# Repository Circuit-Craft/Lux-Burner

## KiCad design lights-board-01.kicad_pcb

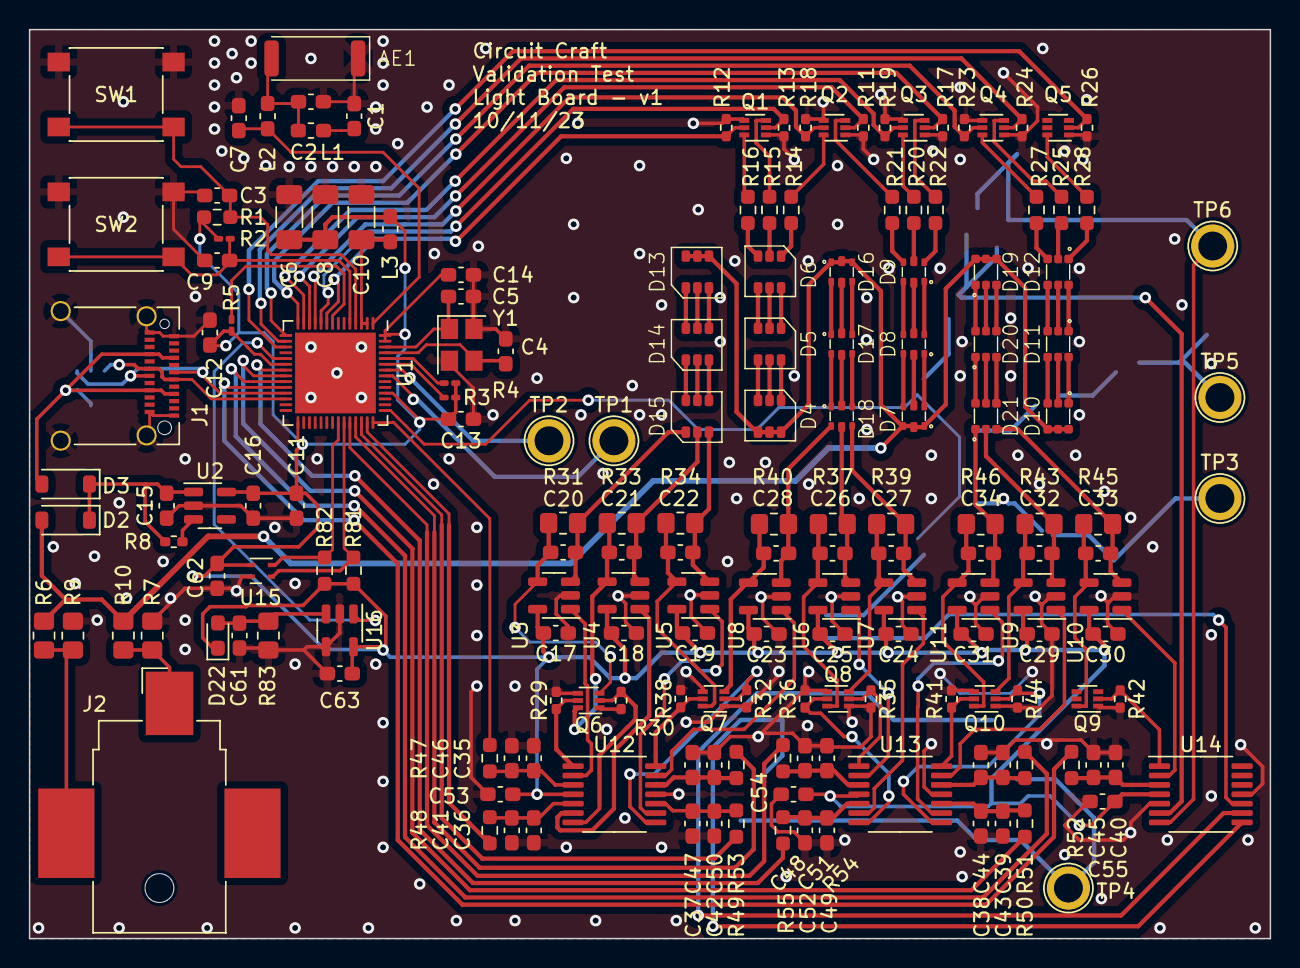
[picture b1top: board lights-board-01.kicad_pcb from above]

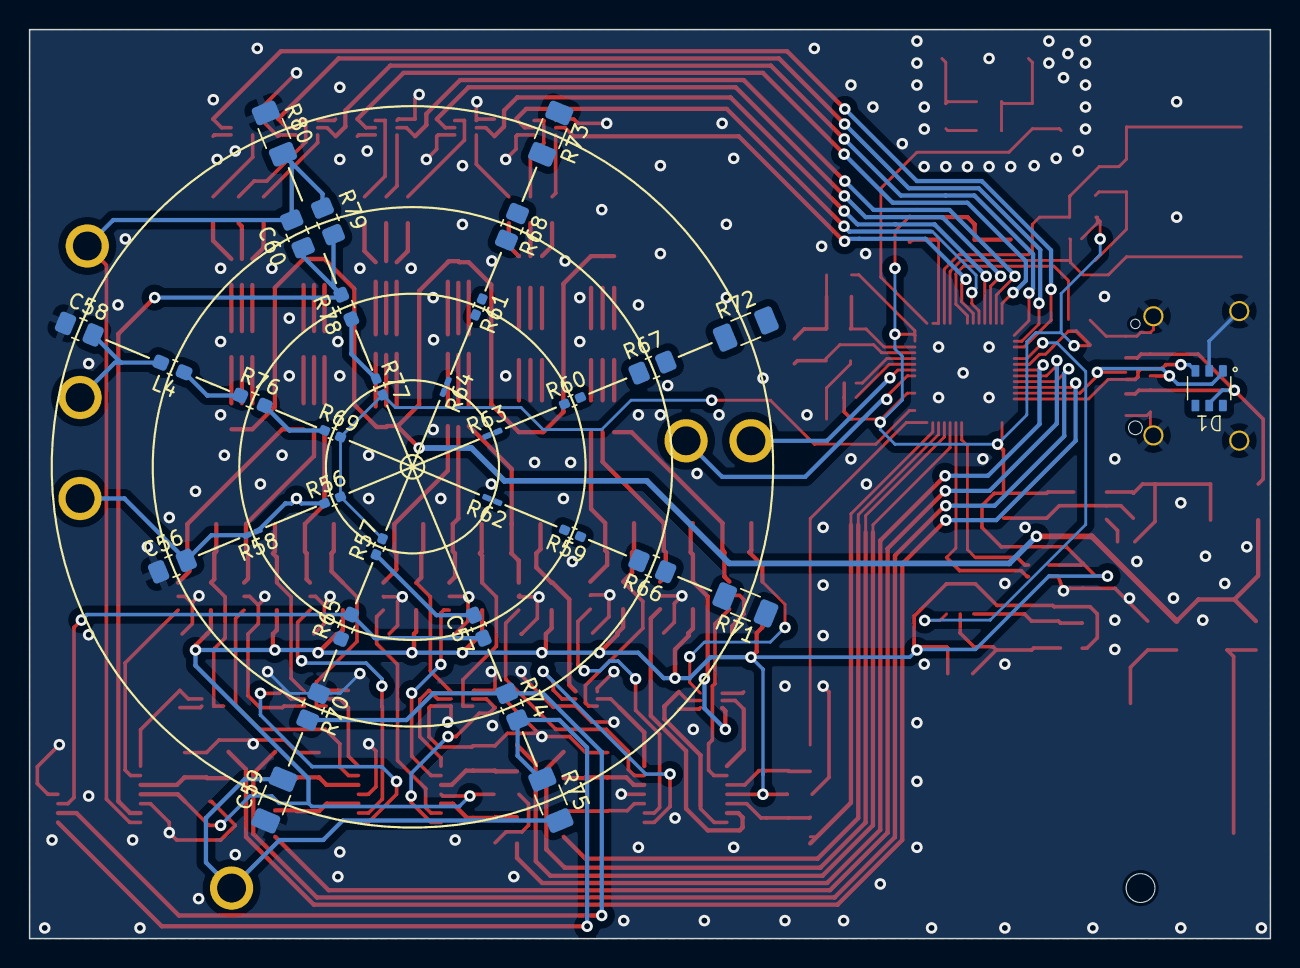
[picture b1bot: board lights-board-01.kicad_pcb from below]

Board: 2 copper layers, 86.0 x 63.0 mm, 210 parts (32 on the bottom side), 158 nets.

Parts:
AE1: Antenna_Chip; 2450AT43B
C1, C2, C3, C4, C5, C7: DNP; C_0603_1608Metric_Pad1.08x0.95mm_HandSolder
C6: 10uF; C_1206_3216Metric_Pad1.33x1.80mm_HandSolder
C8, C10, C59: 0.1uF; C_1206_3216Metric_Pad1.33x1.80mm_HandSolder
C9, C20, C21, C22, C26, C27, C28, C32, C33, C34, C35, C36, C37, C38, C39, C40, C41, C42, C43, C44, C45, C46, C47, C48, C49, C50, C51, C52, C57, C61: 0.1uF; C_0603_1608Metric_Pad1.08x0.95mm_HandSolder
C11, C12, C13, C14, C15, C16, C17, C18, C19, C23, C24, C25, C29, C30, C31, C53, C54, C55, C62, C63: 4.7uF; C_0603_1608Metric_Pad1.08x0.95mm_HandSolder
C56, C60: 0.1uF; C_0805_2012Metric_Pad1.18x1.45mm_HandSolder
C58: 10uF; C_0805_2012Metric_Pad1.18x1.45mm_HandSolder
D1: D5V0F4U6SO; SOT26
D2, D3: 1N4148; D_SOD-123
D4, D5, D6, D13, D14, D15: CLY6D
D7, D8, D9, D16, D17, D18: EAST1616; LED_RGB_EAST_PLCC-6
D10, D11, D12, D19, D20, D21: IN-S66TFT; LED_RGB_Inolux_PLCC-6
D22: IN-S63DTLS; D_0603_1608Metric_Pad1.05x0.95mm_HandSolder
J1: USB_C_Receptacle_USB2.0; USB_C_Receptacle_Amphenol_12401610E4-2A_CircularHoles
J2: Conn_01x02; BarrelJack_CUI_PJ-036AH-SMT_Horizontal
L1, L2: DNP; L_0603_1608Metric_Pad1.05x0.95mm_HandSolder
L3: 2nH; L_0603_1608Metric_Pad1.05x0.95mm_HandSolder
L4: 1uH; L_0603_1608Metric_Pad1.05x0.95mm_HandSolder
Q1, Q2, Q3, Q4, Q5, Q6, Q7, Q8, Q9, Q10: DMN2710UV; SOT-563
R1: DNP; R_0603_1608Metric_Pad0.98x0.95mm_HandSolder
R2, R3, R4, R5: 10k; R_0201_0603Metric_Pad0.64x0.40mm_HandSolder
R6, R7, R66, R67, R68: 0; R_0805_2012Metric_Pad1.20x1.40mm_HandSolder
R8, R11, R12, R13, R17, R18, R19, R23, R24, R26, R29, R30, R32, R35, R36, R38, R41, R42, R44: 100k; R_0402_1005Metric_Pad0.72x0.64mm_HandSolder
R9, R10: DNP; R_0805_2012Metric_Pad1.20x1.40mm_HandSolder
R14: 200; R_0603_1608Metric_Pad0.98x0.95mm_HandSolder
R15, R21, R22: 260; R_0603_1608Metric_Pad0.98x0.95mm_HandSolder
R16: 380; R_0603_1608Metric_Pad0.98x0.95mm_HandSolder
R20: 460; R_0603_1608Metric_Pad0.98x0.95mm_HandSolder
R25: 400; R_0603_1608Metric_Pad0.98x0.95mm_HandSolder
R27, R28: 240; R_0603_1608Metric_Pad0.98x0.95mm_HandSolder
R31, R33: 1.5; R_0805_2012Metric_Pad1.20x1.40mm_HandSolder
R34: 1; R_0805_2012Metric_Pad1.20x1.40mm_HandSolder
R37, R39, R40: 0.75; R_0805_2012Metric_Pad1.20x1.40mm_HandSolder
R43, R45, R46: 3; R_0805_2012Metric_Pad1.20x1.40mm_HandSolder
R47, R48, R49, R50, R51, R52, R53, R54, R55, R65, R76, R78: 1k; R_0603_1608Metric_Pad0.98x0.95mm_HandSolder
R56, R57, R59, R60, R61, R69, R77: 0; R_0402_1005Metric_Pad0.72x0.64mm_HandSolder
R58: 1k; R_0201_0603Metric_Pad0.64x0.40mm_HandSolder
R62, R63, R64: 0; R_0201_0603Metric_Pad0.64x0.40mm_HandSolder
R70, R74, R79: 1k; R_0805_2012Metric_Pad1.20x1.40mm_HandSolder
R71, R72, R73: 0; R_1206_3216Metric_Pad1.30x1.75mm_HandSolder
R75: 1k; R_1206_3216Metric_Pad1.30x1.75mm_HandSolder
R80: 100k; R_1206_3216Metric_Pad1.30x1.75mm_HandSolder
R81, R82: 10k; R_0603_1608Metric_Pad0.98x0.95mm_HandSolder
R83: 5.5k; R_0805_2012Metric_Pad1.20x1.40mm_HandSolder
SW1, SW2: SW_Push; SW_SPST_PTS645
TP1, TP2, TP3, TP4, TP5, TP6: DNP; TestPoint_Plated_Hole_D2.0mm
U1: ESP32-S3; QFN-56-1EP_7x7mm_P0.4mm_EP5.6x5.6mm
U2: AP2202-3.3; SOT-23-5
U3, U4, U5, U6, U7, U8, U9, U10, U11, U16: INA180A4; SOT-23-5
U12, U13, U14: LMV324; TSSOP-14_4.4x5mm_P0.65mm
U15: SHT4x; Sensirion_DFN-4_1.5x1.5mm_P0.8mm_SHT4x_NoCentralPad
Y1: Crystal_GND24; Crystal_SMD_3225-4Pin_3.2x2.5mm

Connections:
+3V3: C6.1, C8.1, C11.1, C12.1, C13.1, C14.1, C16.1, C17.2, C18.2, C19.2, C23.2, C24.2, C25.2, C29.2, C30.2, C31.2, C53.1, C54.1, C55.1, C62.2, C63.2, D22.1 (K), L3.1, R1.1, R2.1, R3.2, R4.2, R5.2, R81.1, R82.1, U1.20 (VDD3P3_RTC), U1.29 (VDD_SPI), U1.46 (VDD3P3_CPU), U1.55 (VDDA), U1.56 (VDDA), U2.5 (VOUT), U3.5 (V+), U4.5 (V+), U5.5 (V+), U6.5 (V+), U7.5 (V+), U8.5 (V+), U9.5 (V+), U10.5 (V+), U11.5 (V+), U12.4 (V+), U13.4 (V+), U14.4 (V+), U15.3 (VDD), U16.5 (V+)
+12V: D2.2 (A), D4.4 (BA), D4.5 (GA), D4.6 (RA), D7.1 (BA), D7.3 (RA), D7.5 (GA), D10.4 (BA), D10.5 (RA), D10.6 (GA), D13.4 (BA), D13.5 (GA), D13.6 (RA), D16.1 (BA), D16.3 (RA), D16.5 (GA), D19.4 (BA), D19.5 (RA), D19.6 (GA), R6.1, R10.2
/LEDs/CH1.B_PWM: Q1.2 (G), R13.1, U1.10 (GPIO5/ADC1_CH4)
/LEDs/CH1.B_PWM_DAC: R48.1, U1.41 (GPIO36)
/LEDs/CH1.G_PWM: Q1.5 (G), R12.1, U1.9 (GPIO4/ADC1_CH3)
/LEDs/CH1.G_PWM_DAC: R49.1, U1.40 (GPIO35)
/LEDs/CH1.R_PWM: Q2.2 (G), R11.1, U1.12 (GPIO7/ADC1_CH6)
/LEDs/CH1.R_PWM_DAC: R47.1, U1.42 (GPIO37)
/LEDs/CH2.B_PWM: Q3.5 (G), R19.1, U1.13 (GPIO8/ADC1_CH7)
/LEDs/CH2.B_PWM_DAC: R55.1, U1.21 (GPIO15/ADC2_CH4/XTAL_32K_P)
/LEDs/CH2.G_PWM: Q2.5 (G), R18.1, U1.11 (GPIO6/ADC1_CH5)
/LEDs/CH2.G_PWM_DAC: R53.1, U1.39 (GPIO34)
/LEDs/CH2.R_PWM: Q3.2 (G), R17.1, U1.14 (GPIO9/ADC1_CH8)
/LEDs/CH2.R_PWM_DAC: R54.1, U1.38 (GPIO33)
/LEDs/CH3.B_PWM: Q5.2 (G), R26.1, U1.17 (GPIO12/ADC2_CH1)
/LEDs/CH3.B_PWM_DAC: R52.1, U1.24 (GPIO18/ADC2_CH7)
/LEDs/CH3.G_PWM: Q4.5 (G), R24.1, U1.16 (GPIO11/ADC2_CH0)
/LEDs/CH3.G_PWM_DAC: R50.1, U1.22 (GPIO16/ADC2_CH5/XTAL_32K_N)
/LEDs/CH3.R_PWM: Q4.2 (G), R23.1, U1.15 (GPIO10/ADC1_CH9)
/LEDs/CH3.R_PWM_DAC: R51.1, U1.23 (GPIO17/ADC2_CH6)
/LEDs/DAC/Control/CH1.B_GATE: Q7.2 (G), R32.1, U12.8
/LEDs/DAC/Control/CH1.B_SENSE: U5.1, U12.9 (-)
/LEDs/DAC/Control/CH1.G_GATE: Q6.2 (G), R30.1, U12.7
/LEDs/DAC/Control/CH1.G_SENSE: U4.1, U12.6 (-)
/LEDs/DAC/Control/CH1.R_GATE: Q6.5 (G), R29.1, U12.1
/LEDs/DAC/Control/CH1.R_SENSE: U3.1, U12.2 (-)
/LEDs/DAC/Control/CH2.B_GATE: Q7.5 (G), R38.1, U12.14
/LEDs/DAC/Control/CH2.B_SENSE: U8.1, U12.13 (-)
/LEDs/DAC/Control/CH2.G_GATE: Q8.2 (G), R36.1, U13.7
/LEDs/DAC/Control/CH2.G_SENSE: U7.1, U13.6 (-)
/LEDs/DAC/Control/CH2.R_GATE: Q8.5 (G), R35.1, U13.1
/LEDs/DAC/Control/CH2.R_SENSE: U6.1, U13.2 (-)
/LEDs/DAC/Control/CH3.B_GATE: Q10.2 (G), R44.1, U13.8
/LEDs/DAC/Control/CH3.B_SENSE: U11.1, U13.9 (-)
/LEDs/DAC/Control/CH3.G_GATE: Q9.2 (G), R42.1, U14.1
/LEDs/DAC/Control/CH3.G_SENSE: U10.1, U14.2 (-)
/LEDs/DAC/Control/CH3.R_GATE: Q10.5 (G), R41.1, U13.14
/LEDs/DAC/Control/CH3.R_SENSE: U9.1, U13.13 (-)
/LEDs/SIG_FILTER: R56.2, R57.2, R69.2, R77.2, U1.43 (GPIO38)
/MCU/BOOT: C9.1, R2.2, SW2.2, U1.5 (GPIO0/BOOT)
/MCU/GPIO14/A2.3: U1.19 (GPIO14/ADC2_CH3), U16.1
/MCU/GPIO47: R81.2, U1.37 (SPICLK_P/GPIO47), U15.1 (SDA)
/MCU/GPIO48: R82.2, U1.36 (SPICLK_N/GPIO48), U15.2 (SCL)
/MCU/RESET: C3.1, R1.2, SW1.2, U1.4 (CHIP_PU/RESET)
/Power/V_in: C15.1, D2.1 (K), D3.1 (K), R8.1, U2.1 (VIN)
GND: AE1.1 (FEED), C1.2, C2.2, C3.2, C4.1, C5.2, C6.2, C7.2, C8.2, C9.2, C10.2, C11.2, C12.2, C13.2, C14.2, C15.2, C16.2, C17.1, C18.1, C19.1, C23.1, C24.1, C25.1, C29.1, C30.1, C31.1, C35.2, C36.2, C37.2, C38.2, C39.2, C40.2, C41.2, C42.2, C43.2, C44.2, C45.2, C46.2, C47.2, C48.2, C49.2, C50.2, C51.2, C52.2, C53.2, C54.2, C55.2, C56.1, C58.1, C59.1, C61.2, C62.1, C63.1, D1.2 (A), J1.A1 (GND), J1.A12 (GND), J1.B1 (GND), J1.B12 (GND), J1.S1 (SHIELD), Q1.1 (S), Q1.4 (S), Q2.1 (S), Q2.4 (S), Q3.1 (S), Q3.4 (S), Q4.1 (S), Q4.4 (S), Q5.1 (S), Q6.1 (S), Q6.4 (S), Q7.1 (S), Q7.4 (S), Q8.1 (S), Q8.4 (S), Q9.1 (S), Q10.1 (S), Q10.4 (S), R7.2, R9.1, R11.2, R12.2, R13.2, R17.2, R18.2, R19.2, R23.2, R24.2, R26.2, R29.2, R30.2, R32.2, R35.2, R36.2, R38.2, R41.2, R42.2, R44.2, R65.1, R70.1, R80.1, R83.2, SW1.1, SW2.1, U1.57 (GND), U2.2 (GND), U3.2 (GND), U4.2 (GND), U5.2 (GND), U6.2 (GND), U7.2 (GND), U8.2 (GND), U9.2 (GND), U10.2 (GND), U11.2 (GND), U12.11 (V-), U13.11 (V-), U14.5 (+), U14.11 (V-), U15.4 (VSS), U16.2 (GND), U16.4 (-), Y1.2, Y1.4
unnamed: AE1.2 (PCB_Trace), C2.1, L1.1, L2.1
unnamed: C1.1, L1.2
unnamed: C56.2, R58.2, TP3.1
unnamed: C57.2, R57.1
unnamed: C58.2, L4.2, TP5.1
unnamed: C59.2, R75.2, TP4.1
unnamed: C60.1, R79.2, R80.2, TP6.1, U14.7
unnamed: D1.1 (K1), J1.A6 (D+), J1.B6 (D+), U1.25 (GPIO19/USB_D-/ADC2_CH8)
unnamed: D1.3 (K2), J1.A7 (D-), J1.B7 (D-), U1.26 (GPIO20/USB_D+/ADC2_CH9)
unnamed: D4.3 (BK), D5.4 (BA)
unnamed: D4.2 (GK), D5.5 (GA)
unnamed: D4.1 (RK), D5.6 (RA)
unnamed: D5.3 (BK), D6.4 (BA)
unnamed: D5.2 (GK), D6.5 (GA)
unnamed: D5.1 (RK), D6.6 (RA)
unnamed: D6.3 (BK), R16.1
unnamed: D6.2 (GK), R15.1
unnamed: D6.1 (RK), R14.1
unnamed: D7.2 (BK), D8.1 (BA)
unnamed: D7.6 (GK), D8.5 (GA)
unnamed: D7.4 (RK), D8.3 (RA)
unnamed: D8.2 (BK), D9.1 (BA)
unnamed: D8.6 (GK), D9.5 (GA)
unnamed: D8.4 (RK), D9.3 (RA)
unnamed: D9.2 (BK), R22.1
unnamed: D9.6 (GK), R21.1
unnamed: D9.4 (RK), R20.1
unnamed: D10.1 (BK), D11.4 (BA)
unnamed: D10.3 (GK), D11.6 (GA)
unnamed: D10.2 (RK), D11.5 (RA)
unnamed: D11.1 (BK), D12.4 (BA)
unnamed: D11.3 (GK), D12.6 (GA)
unnamed: D11.2 (RK), D12.5 (RA)
unnamed: D12.1 (BK), R28.1
unnamed: D12.3 (GK), R27.1
unnamed: D12.2 (RK), R25.1
unnamed: D13.3 (BK), D14.4 (BA)
unnamed: D13.2 (GK), D14.5 (GA)
unnamed: D13.1 (RK), D14.6 (RA)
unnamed: D14.3 (BK), D15.4 (BA)
unnamed: D14.2 (GK), D15.5 (GA)
unnamed: D14.1 (RK), D15.6 (RA)
unnamed: C22.1, D15.3 (BK), R34.1, U5.3 (+)
unnamed: C21.1, D15.2 (GK), R33.1, U4.3 (+)
unnamed: C20.1, D15.1 (RK), R31.1, U3.3 (+)
unnamed: D16.2 (BK), D17.1 (BA)
unnamed: D16.6 (GK), D17.5 (GA)
unnamed: D16.4 (RK), D17.3 (RA)
unnamed: D17.2 (BK), D18.1 (BA)
unnamed: D17.6 (GK), D18.5 (GA)
unnamed: D17.4 (RK), D18.3 (RA)
unnamed: C28.1, D18.2 (BK), R40.1, U8.3 (+)
unnamed: C27.1, D18.6 (GK), R39.1, U7.3 (+)
unnamed: C26.1, D18.4 (RK), R37.1, U6.3 (+)
unnamed: D19.1 (BK), D20.4 (BA)
unnamed: D19.3 (GK), D20.6 (GA)
unnamed: D19.2 (RK), D20.5 (RA)
unnamed: D20.1 (BK), D21.4 (BA)
unnamed: D20.3 (GK), D21.6 (GA)
unnamed: D20.2 (RK), D21.5 (RA)
unnamed: C34.1, D21.1 (BK), R46.1, U11.3 (+)
unnamed: C33.1, D21.3 (GK), R45.1, U10.3 (+)
unnamed: C32.1, D21.2 (RK), R43.1, U9.3 (+)
unnamed: C61.1, D22.2 (A), R83.1, U16.3 (+)
unnamed: J2.1, R7.1, R10.1
unnamed: J2.2, R6.2, R9.2
unnamed: L4.1, R76.1
unnamed: Q1.6 (D), R16.2
unnamed: Q1.3 (D), R15.2
unnamed: Q2.6 (D), R14.2
unnamed: Q2.3 (D), R21.2
unnamed: Q3.6 (D), R20.2
unnamed: Q3.3 (D), R22.2
unnamed: Q4.6 (D), R25.2
unnamed: Q4.3 (D), R27.2
unnamed: Q5.6 (D), R28.2
unnamed: C21.2, Q6.6 (D), R33.2, U4.4 (-)
unnamed: C20.2, Q6.3 (D), R31.2, U3.4 (-)
unnamed: C22.2, Q7.6 (D), R34.2, U5.4 (-)
unnamed: C28.2, Q7.3 (D), R40.2, U8.4 (-)
unnamed: C27.2, Q8.6 (D), R39.2, U7.4 (-)
unnamed: C26.2, Q8.3 (D), R37.2, U6.4 (-)
unnamed: C33.2, Q9.6 (D), R45.2, U10.4 (-)
unnamed: C34.2, Q10.6 (D), R46.2, U11.4 (-)
unnamed: C32.2, Q10.3 (D), R43.2, U9.4 (-)
unnamed: R56.1, R58.1
unnamed: R69.1, R76.2
unnamed: R74.2, R75.1, U14.8
unnamed: R77.1, R78.1
unnamed: R5.1, U1.8 (GPIO3/ADC1_CH2)
unnamed: R3.1, U1.51 (GPIO45)
unnamed: R4.1, U1.52 (GPIO46)
unnamed: C7.1, L2.2, U1.1 (LNA_IN/RF)
unnamed: TP2.1, U1.50 (U0RXD/PROG/GPIO44)
unnamed: TP1.1, U1.49 (U0TXD/PROG/GPIO43)
unnamed: C4.2, U1.53 (XTAL_N), Y1.3
unnamed: C5.1, U1.54 (XTAL_P), Y1.1
unnamed: R8.2, U2.3 (INH)
unnamed: C35.1, C46.1, R47.2, U12.3 (+)
unnamed: C36.1, C41.1, R48.2, U12.5 (+)
unnamed: C37.1, C42.1, R49.2, U12.10 (+)
unnamed: C47.1, C50.1, R53.2, U12.12 (+)
unnamed: C48.1, C51.1, R54.2, U13.3 (+)
unnamed: C49.1, C52.1, R55.2, U13.5 (+)
unnamed: C38.1, C43.1, R50.2, U13.10 (+)
unnamed: C39.1, C44.1, R51.2, U13.12 (+)
unnamed: C40.1, C45.1, R52.2, U14.3 (+)
unnamed: C60.2, R78.2, R79.1, U14.6 (-)
unnamed: C57.1, R65.2, U14.10 (+)
unnamed: R70.2, R74.1, U14.9 (-)
VBUS: D1.5 (K_Vcc), D3.2 (A), J1.A4 (VBUS), J1.A9 (VBUS), J1.B4 (VBUS), J1.B9 (VBUS)
VDD3P3: C10.1, L3.2, U1.2 (VDD3P3), U1.3 (VDD3P3)
